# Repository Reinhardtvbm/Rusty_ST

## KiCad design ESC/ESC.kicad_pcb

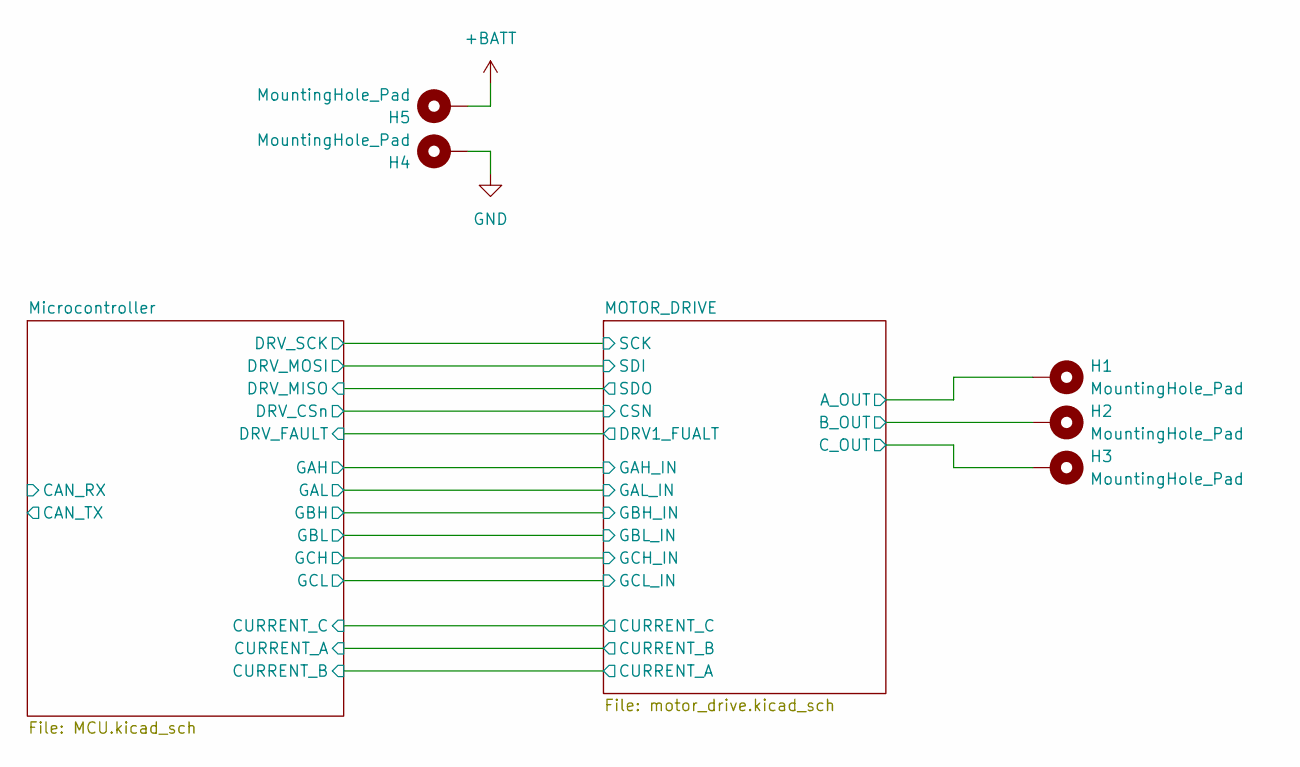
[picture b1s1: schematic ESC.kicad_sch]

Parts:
H1, H2, H3: MountingHole_Pad; Pad_3x4
H4, H5: MountingHole_Pad; Pad_THT_3x4

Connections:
+BATT: H5.1; also elsewhere on the board
/MOTOR_DRIVE/A_OUT: H1.1; also elsewhere on the board
/MOTOR_DRIVE/B_OUT: H2.1; also elsewhere on the board
/MOTOR_DRIVE/C_OUT: H3.1; also elsewhere on the board
GND: H4.1; also elsewhere on the board

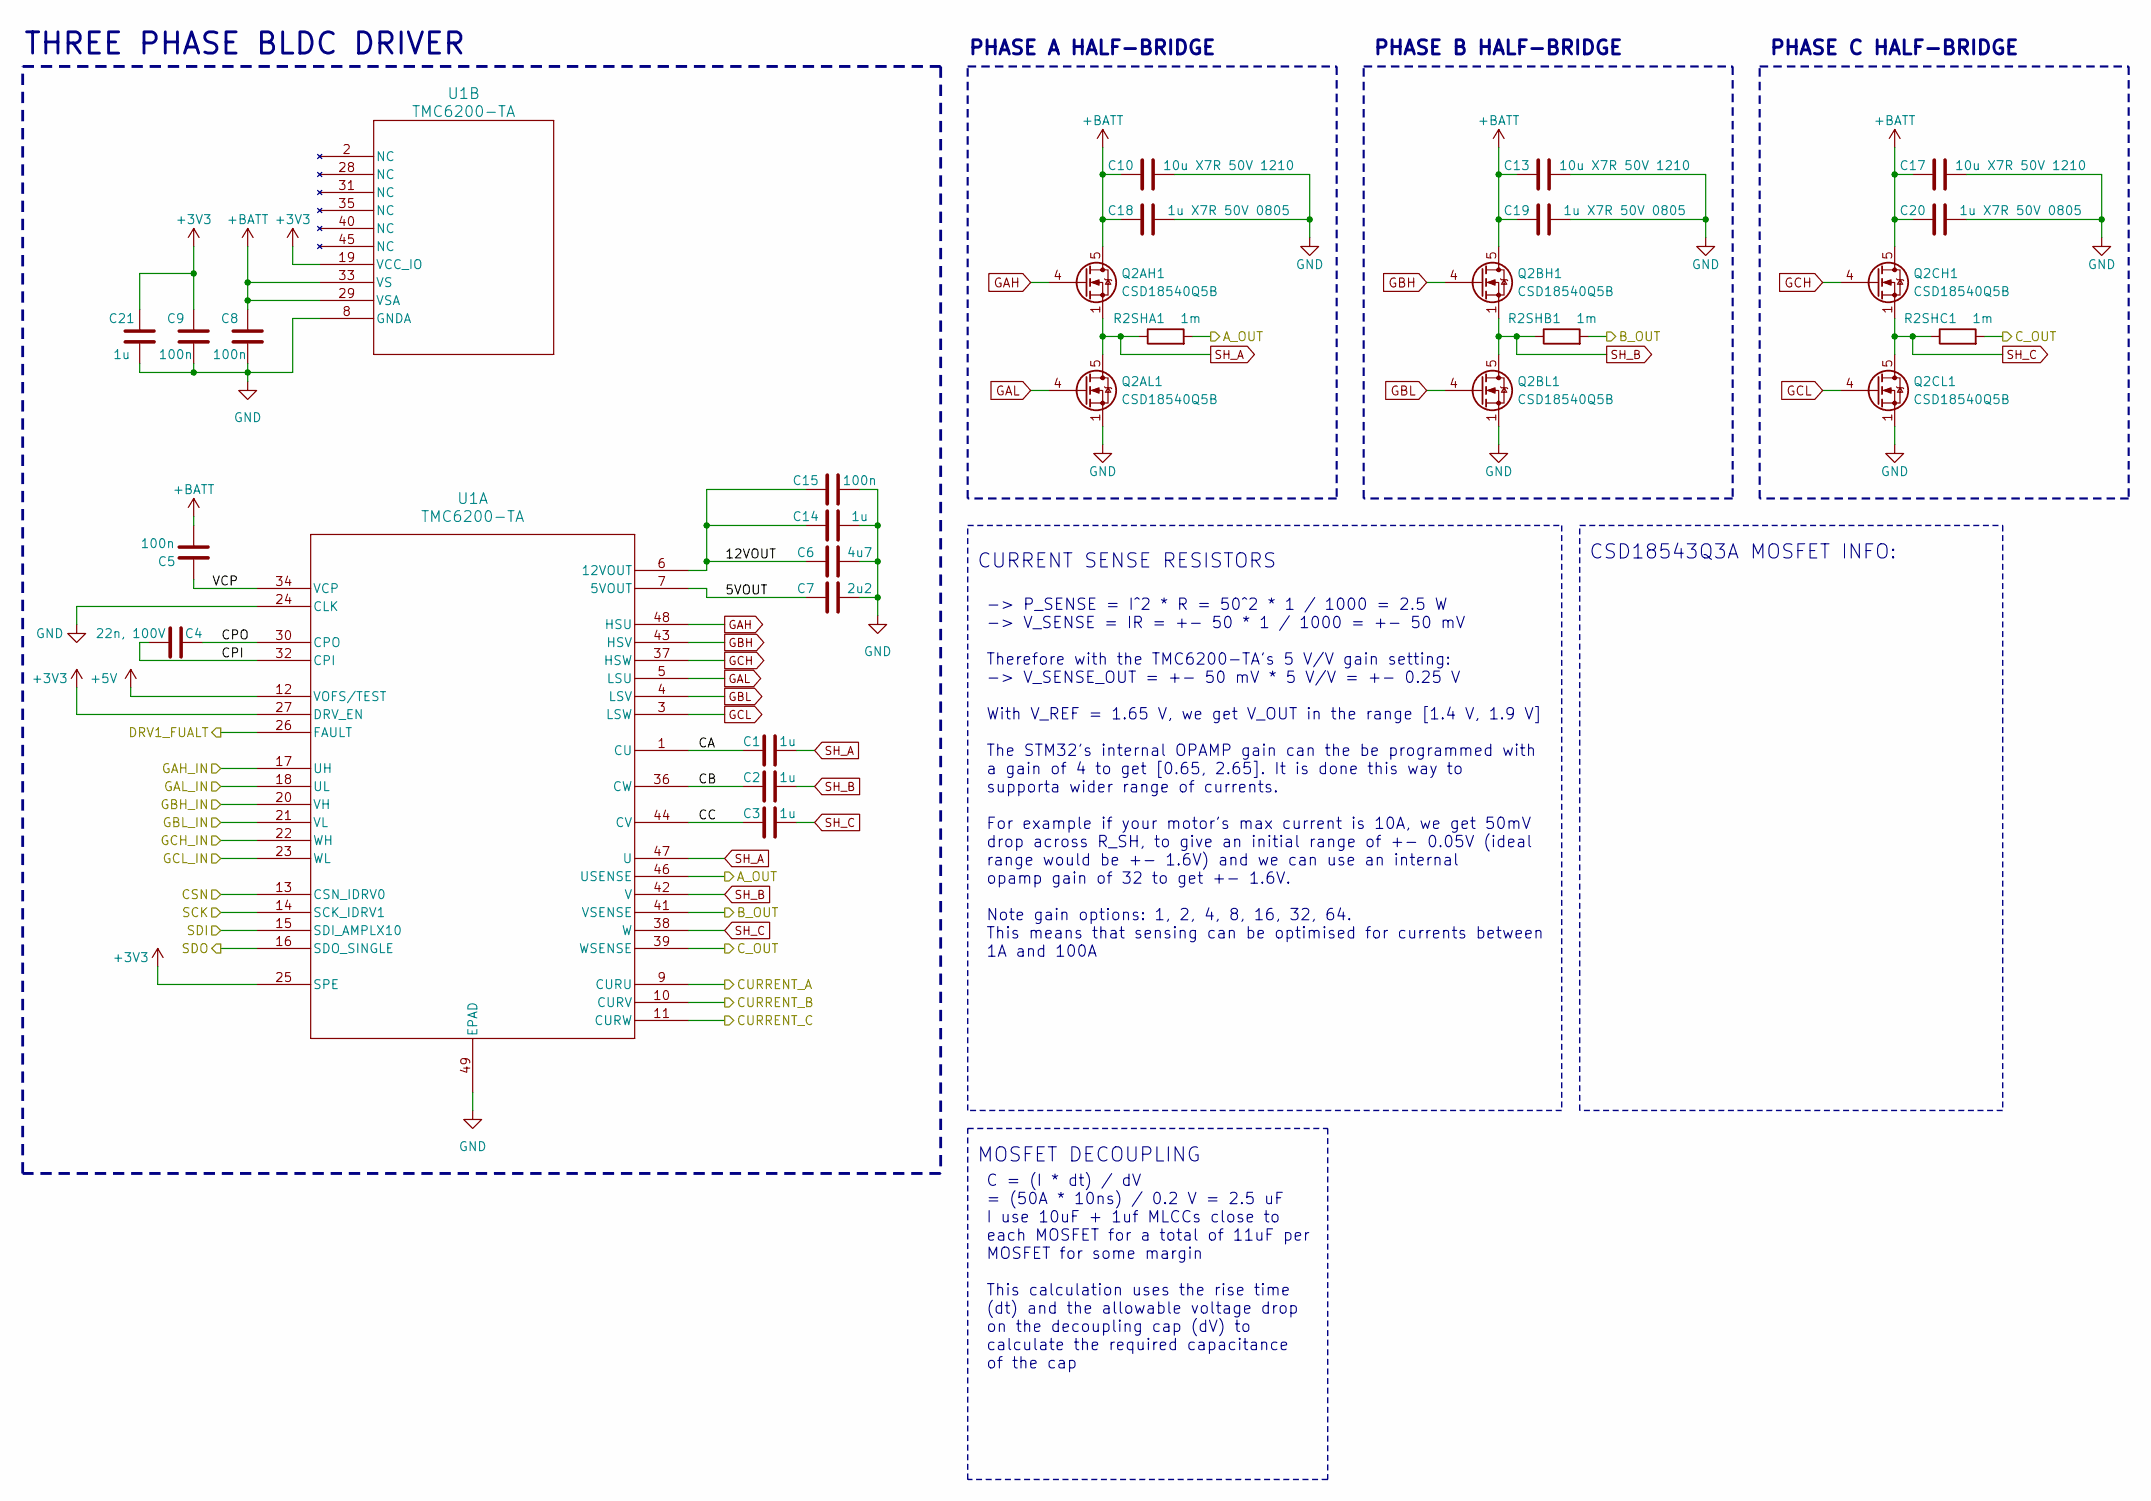
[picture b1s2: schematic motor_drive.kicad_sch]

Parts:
C1, C2, C3: 1u; C_0603_1608Metric
C4: 22n, 100V; C_0603_1608Metric
C5: 100n; C_0603_1608Metric
C6: 4u7; C_0603_1608Metric
C7: 2u2; C_0402_1005Metric
C8: 100n; C_0402_1005Metric
C9, C15: 100n; C_0201_0603Metric
C10, C13, C17: 10u X7R 50V 1210; C_1210_3225Metric
C14: 1u; C_0402_1005Metric
C18, C19, C20: 1u X7R 50V 0805; C_0805_2012Metric
C21: 1u; C_0201_0603Metric
Q2AH1, Q2AL1, Q2BH1, Q2BL1, Q2CH1, Q2CL1: CSD18540Q5B; TDSON-8-1
R2SHA1, R2SHB1, R2SHC1: 1m; R_2512_6332Metric
U1: TMC6200-TA; TQFP-48-1EP_7x7mm_P0.5mm_EP5x5mm

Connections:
+3V3: C9.2, C21.2, U1.19 (VCC_IO), U1.25 (SPE), U1.27 (DRV_EN); also elsewhere on the board
+5V: U1.12 (VOFS/TEST); also elsewhere on the board
+BATT: C5.2, C8.2, C10.1, C13.1, C17.1, C18.1, C19.1, C20.1, Q2AH1.5 (D), Q2BH1.5 (D), Q2CH1.5 (D), U1.29 (VSA), U1.33 (VS); also elsewhere on the board
/MOTOR_DRIVE/5VOUT: C7.2, U1.7 (5VOUT)
/MOTOR_DRIVE/12VOUT: C6.1, C14.2, C15.2, U1.6 (12VOUT)
/MOTOR_DRIVE/A_OUT: R2SHA1.2, U1.46 (USENSE); also elsewhere on the board
/MOTOR_DRIVE/B_OUT: R2SHB1.2, U1.41 (VSENSE); also elsewhere on the board
/MOTOR_DRIVE/CA: C1.1, U1.1 (CU)
/MOTOR_DRIVE/CB: C2.1, U1.36 (CW)
/MOTOR_DRIVE/CC: C3.1, U1.44 (CV)
/MOTOR_DRIVE/CPI: C4.2, U1.32 (CPI)
/MOTOR_DRIVE/CPO: C4.1, U1.30 (CPO)
/MOTOR_DRIVE/CSN: U1.13 (CSN_IDRV0); also elsewhere on the board
/MOTOR_DRIVE/CURRENT_A: U1.9 (CURU); also elsewhere on the board
/MOTOR_DRIVE/CURRENT_B: U1.10 (CURV); also elsewhere on the board
/MOTOR_DRIVE/CURRENT_C: U1.11 (CURW); also elsewhere on the board
/MOTOR_DRIVE/C_OUT: R2SHC1.2, U1.39 (WSENSE); also elsewhere on the board
/MOTOR_DRIVE/DRV1_FUALT: U1.26 (FAULT); also elsewhere on the board
/MOTOR_DRIVE/GAH_IN: U1.17 (UH); also elsewhere on the board
/MOTOR_DRIVE/GAL_IN: U1.18 (UL); also elsewhere on the board
/MOTOR_DRIVE/GBH_IN: U1.20 (VH); also elsewhere on the board
/MOTOR_DRIVE/GBL_IN: U1.21 (VL); also elsewhere on the board
/MOTOR_DRIVE/GCH_IN: U1.22 (WH); also elsewhere on the board
/MOTOR_DRIVE/GCL_IN: U1.23 (WL); also elsewhere on the board
/MOTOR_DRIVE/SCK: U1.14 (SCK_IDRV1); also elsewhere on the board
/MOTOR_DRIVE/SDI: U1.15 (SDI_AMPLX10); also elsewhere on the board
/MOTOR_DRIVE/SDO: U1.16 (SDO_SINGLE); also elsewhere on the board
/MOTOR_DRIVE/VCP: C5.1, U1.34 (VCP)
GAH: Q2AH1.4 (G), U1.48 (HSU)
GAL: Q2AL1.4 (G), U1.5 (LSU)
GBH: Q2BH1.4 (G), U1.43 (HSV)
GBL: Q2BL1.4 (G), U1.4 (LSV)
GCH: Q2CH1.4 (G), U1.37 (HSW)
GCL: Q2CL1.4 (G), U1.3 (LSW)
GND: C6.2, C7.1, C8.1, C9.1, C10.2, C13.2, C14.1, C15.1, C17.2, C18.2, C19.2, C20.2, C21.1, Q2AL1.1 (S), Q2AL1.2 (S), Q2AL1.3 (S), Q2BL1.1 (S), Q2BL1.2 (S), Q2BL1.3 (S), Q2CL1.1 (S), Q2CL1.2 (S), Q2CL1.3 (S), U1.8 (GNDA), U1.24 (CLK), U1.49 (EPAD); also elsewhere on the board
SH_A: C1.2, Q2AH1.1 (S), Q2AH1.2 (S), Q2AH1.3 (S), Q2AL1.5 (D), R2SHA1.1, U1.47 (U)
SH_B: C2.2, Q2BH1.1 (S), Q2BH1.2 (S), Q2BH1.3 (S), Q2BL1.5 (D), R2SHB1.1, U1.42 (V)
SH_C: C3.2, Q2CH1.1 (S), Q2CH1.2 (S), Q2CH1.3 (S), Q2CL1.5 (D), R2SHC1.1, U1.38 (W)

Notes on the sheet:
C = (I * dt) / dV = (50A * 10ns) / 0.2 V = 2.5 uF I use 10uF + 1uf MLCCs close to each MOSFET for a total of 11uF per MOSFET for some margin This calculation uses the rise time (dt) and the allowable voltage drop on the decoupling cap (dV) to calculate the required capacitance of the cap
-> P_SENSE = I^2 * R = 50^2 * 1 / 1000 = 2.5 W -> V_SENSE = IR = +- 50 * 1 / 1000 = +- 50 mV Therefore with the TMC6200-TA's 5 V/V gain setting: -> V_SENSE_OUT = +- 50 mV * 5 V/V = +- 0.25 V With V_REF = 1.65 V, we get V_OUT in the range [1.4 V, 1.9 V] The STM32's internal OPAMP gain can the be pro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
PHASE C HALF-BRIDGE
CURRENT SENSE RESISTORS
CSD18543Q3A MOSFET INFO:
PHASE B HALF-BRIDGE
THREE PHASE BLDC DRIVER
PHASE A HALF-BRIDGE
MOSFET DECOUPLING

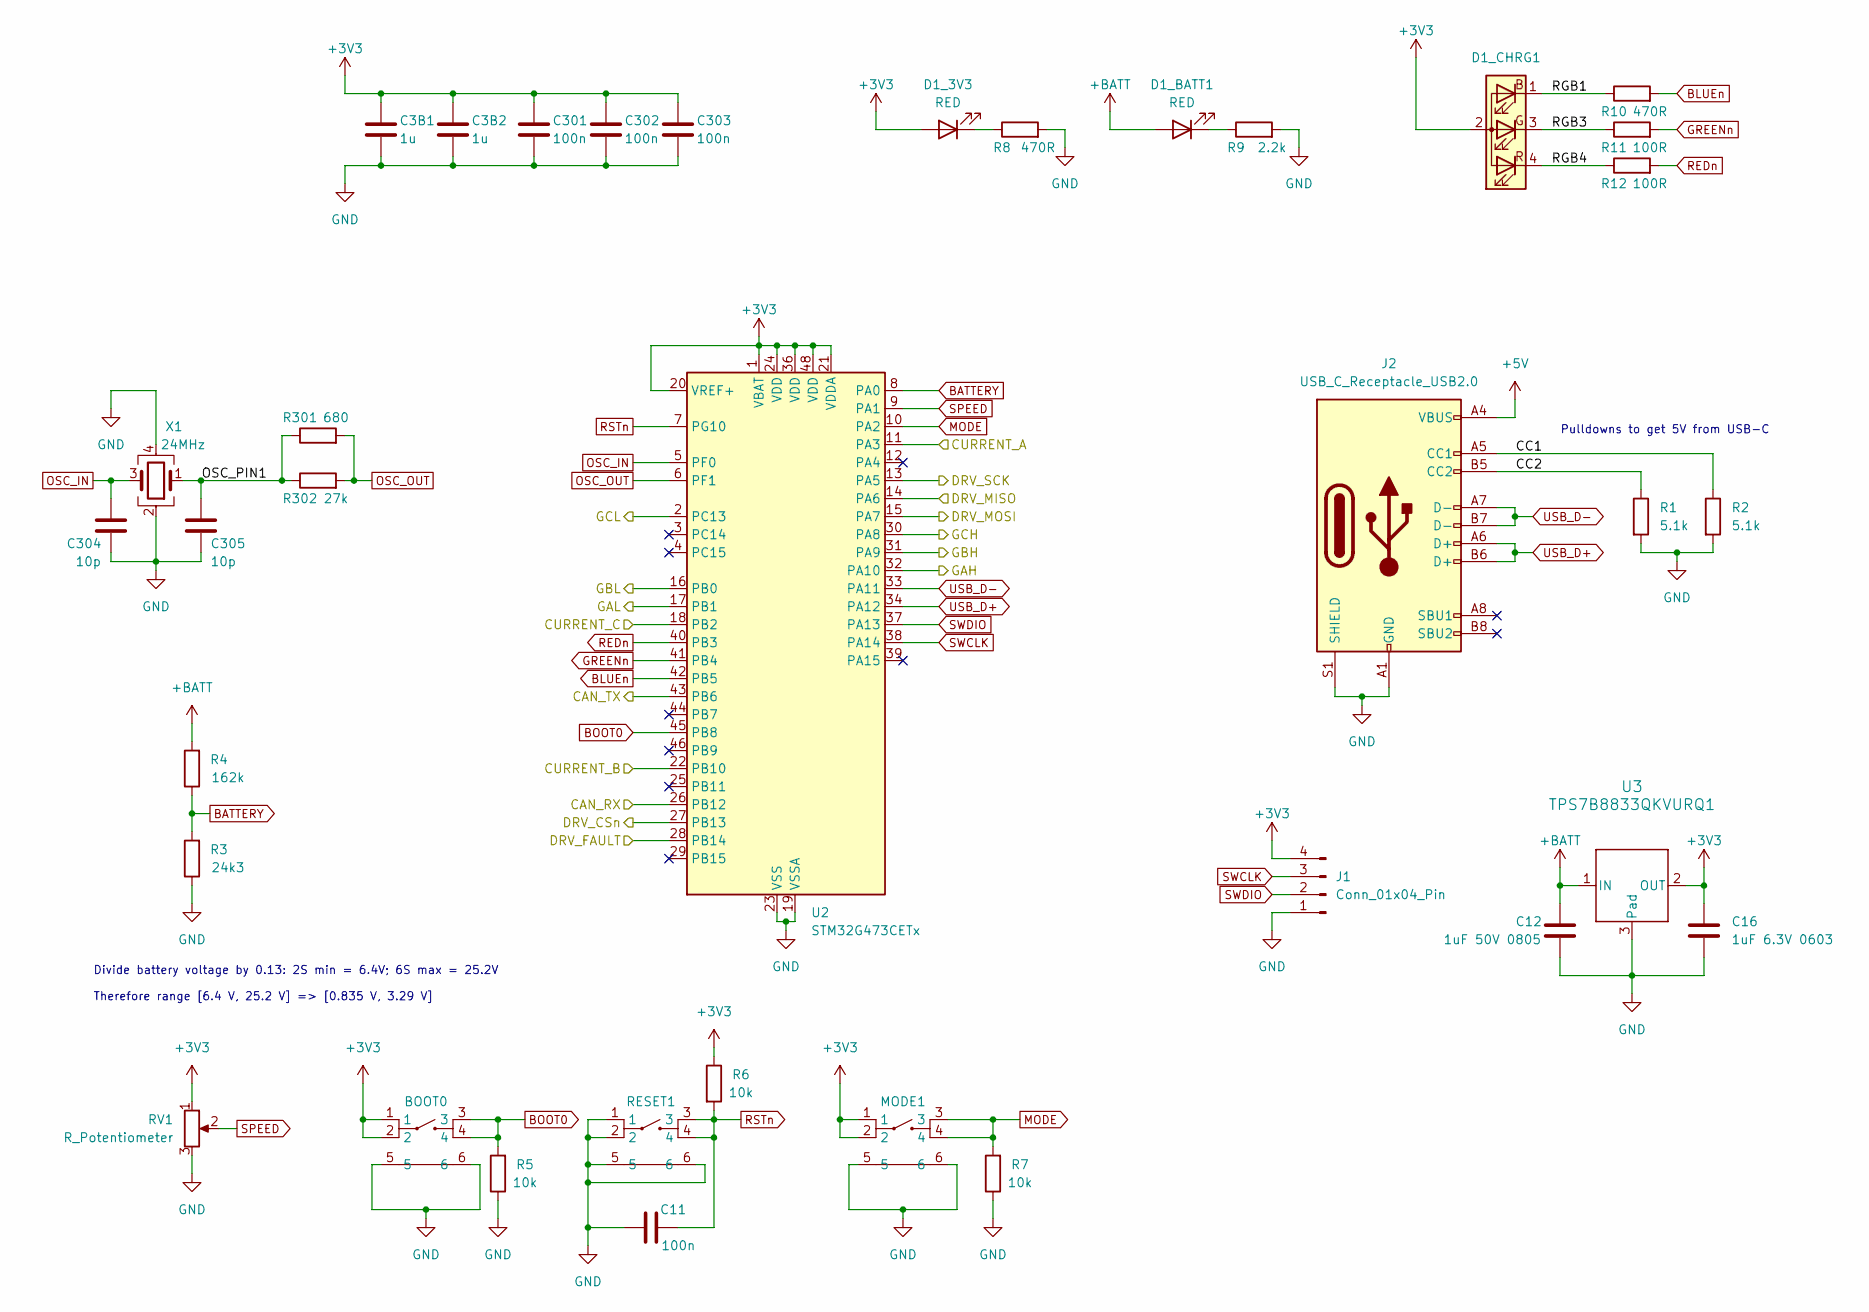
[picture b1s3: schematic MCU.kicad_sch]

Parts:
BOOT0: 435151014824; Wurth
C3B1, C3B2: 1u; C_0201_0603Metric
C11: 100n; C_0603_1608Metric
C12: 1uF 50V 0805; C_0805_2012Metric
C16: 1uF 6.3V 0603; C_0603_1608Metric
C301, C302, C303: 100n; C_0201_0603Metric
C304, C305: 10p; C_0603_1608Metric
D1_3V3, D1_BATT1: RED; LED_0603_1608Metric
D1_CHRG1: LED_BAGR; 150120M173000
J1: Conn_01x04_Pin; PinHeader_1x04_P2.54mm_Vertical
J2: USB_C_Receptacle_USB2.0; USB_C_Receptacle_GCT_USB4105-xx-A_16P_TopMnt_Horizontal
MODE1: 435151014824; Wurth
R1, R2: 5.1k; R_0603_1608Metric
R3: 24k3; R_0603_1608Metric
R4: 162k; R_0603_1608Metric
R5, R6, R7: 10k; R_0603_1608Metric
R8, R10: 470R; R_0603_1608Metric
R9: 2.2k; R_0603_1608Metric
R11, R12: 100R; R_0603_1608Metric
R301: 680; R_0603_1608Metric
R302: 27k; R_0603_1608Metric
RESET1: 435151014824; Wurth
RV1: R_Potentiometer; Potentiometer_Alps_RK09Y11_Single_Horizontal
U2: STM32G473CETx; LQFP-48_7x7mm_P0.5mm
U3: TPS7B8833QKVURQ1; KVU0003A-MFG
X1: 24MHz; Crystal_SMD_3225-4Pin_3.2x2.5mm

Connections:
+3V3: BOOT0.1, BOOT0.2, C3B1.1, C3B2.1, C16.1, C301.1, C302.1, C303.1, D1_3V3.2 (A), D1_CHRG1.2 (A), J1.4, MODE1.1, MODE1.2, R6.1, RV1.1, U2.1 (VBAT), U2.20 (VREF+), U2.21 (VDDA), U2.24 (VDD), U2.36 (VDD), U2.48 (VDD), U3.2 (OUT); also elsewhere on the board
+5V: J2.A4 (VBUS), J2.A9 (VBUS), J2.B4 (VBUS), J2.B9 (VBUS); also elsewhere on the board
+BATT: C12.1, D1_BATT1.2 (A), R4.2, U3.1 (IN); also elsewhere on the board
/MOTOR_DRIVE/CSN: U2.27 (PB13); also elsewhere on the board
/MOTOR_DRIVE/CURRENT_A: U2.22 (PB10); also elsewhere on the board
/MOTOR_DRIVE/CURRENT_B: U2.11 (PA3); also elsewhere on the board
/MOTOR_DRIVE/CURRENT_C: U2.18 (PB2); also elsewhere on the board
/MOTOR_DRIVE/DRV1_FUALT: U2.28 (PB14); also elsewhere on the board
/MOTOR_DRIVE/GAH_IN: U2.32 (PA10); also elsewhere on the board
/MOTOR_DRIVE/GAL_IN: U2.17 (PB1); also elsewhere on the board
/MOTOR_DRIVE/GBH_IN: U2.31 (PA9); also elsewhere on the board
/MOTOR_DRIVE/GBL_IN: U2.16 (PB0); also elsewhere on the board
/MOTOR_DRIVE/GCH_IN: U2.30 (PA8); also elsewhere on the board
/MOTOR_DRIVE/GCL_IN: U2.2 (PC13); also elsewhere on the board
/MOTOR_DRIVE/SCK: U2.13 (PA5); also elsewhere on the board
/MOTOR_DRIVE/SDI: U2.15 (PA7); also elsewhere on the board
/MOTOR_DRIVE/SDO: U2.14 (PA6); also elsewhere on the board
/Microcontroller/CAN_RX: U2.26 (PB12)
/Microcontroller/CAN_TX: U2.43 (PB6)
/Microcontroller/CC1: J2.A5 (CC1), R2.1
/Microcontroller/CC2: J2.B5 (CC2), R1.1
/Microcontroller/OSC_PIN1: C305.1, R301.1, R302.1, X1.1
/Microcontroller/RGB1: D1_CHRG1.1 (BK), R10.1
/Microcontroller/RGB3: D1_CHRG1.3 (GK), R11.1
/Microcontroller/RGB4: D1_CHRG1.4 (RK), R12.1
BATTERY: R3.2, R4.1, U2.8 (PA0)
BLUEn: R10.2, U2.42 (PB5)
BOOT0: BOOT0.3, BOOT0.4, R5.2, U2.45 (PB8)
GND: BOOT0.5, BOOT0.6, C3B1.2, C3B2.2, C11.1, C12.2, C16.2, C301.2, C302.2, C303.2, C304.2, C305.2, J1.1, J2.A1 (GND), J2.A12 (GND), J2.B1 (GND), J2.B12 (GND), J2.S1 (SHIELD), MODE1.5, MODE1.6, R1.2, R2.2, R3.1, R5.1, R7.1, R8.2, R9.2, RESET1.1, RESET1.2, RESET1.5, RESET1.6, RV1.3, U2.19 (VSSA), U2.23 (VSS), U2.35 (VSS), U2.47 (VSS), U3.3 (Pad), X1.2, X1.4; also elsewhere on the board
GREENn: R11.2, U2.41 (PB4)
MODE: MODE1.3, MODE1.4, R7.2, U2.10 (PA2)
unnamed: D1_3V3.1 (K), R8.1
unnamed: D1_BATT1.1 (K), R9.1
OSC_IN: C304.1, U2.5 (PF0), X1.3
OSC_OUT: R301.2, R302.2, U2.6 (PF1)
REDn: R12.2, U2.40 (PB3)
RSTn: C11.2, R6.2, RESET1.3, RESET1.4, U2.7 (PG10)
SPEED: RV1.2, U2.9 (PA1)
SWCLK: J1.3, U2.38 (PA14)
SWDIO: J1.2, U2.37 (PA13)
USB_D+: J2.A6 (D+), J2.B6 (D+), U2.34 (PA12)
USB_D-: J2.A7 (D-), J2.B7 (D-), U2.33 (PA11)

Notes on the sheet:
Divide battery voltage by 0.13: 2S min = 6.4V; 6S max = 25.2V Therefore range [6.4 V, 25.2 V] => [0.835 V, 3.29 V]
Pulldowns to get 5V from USB-C

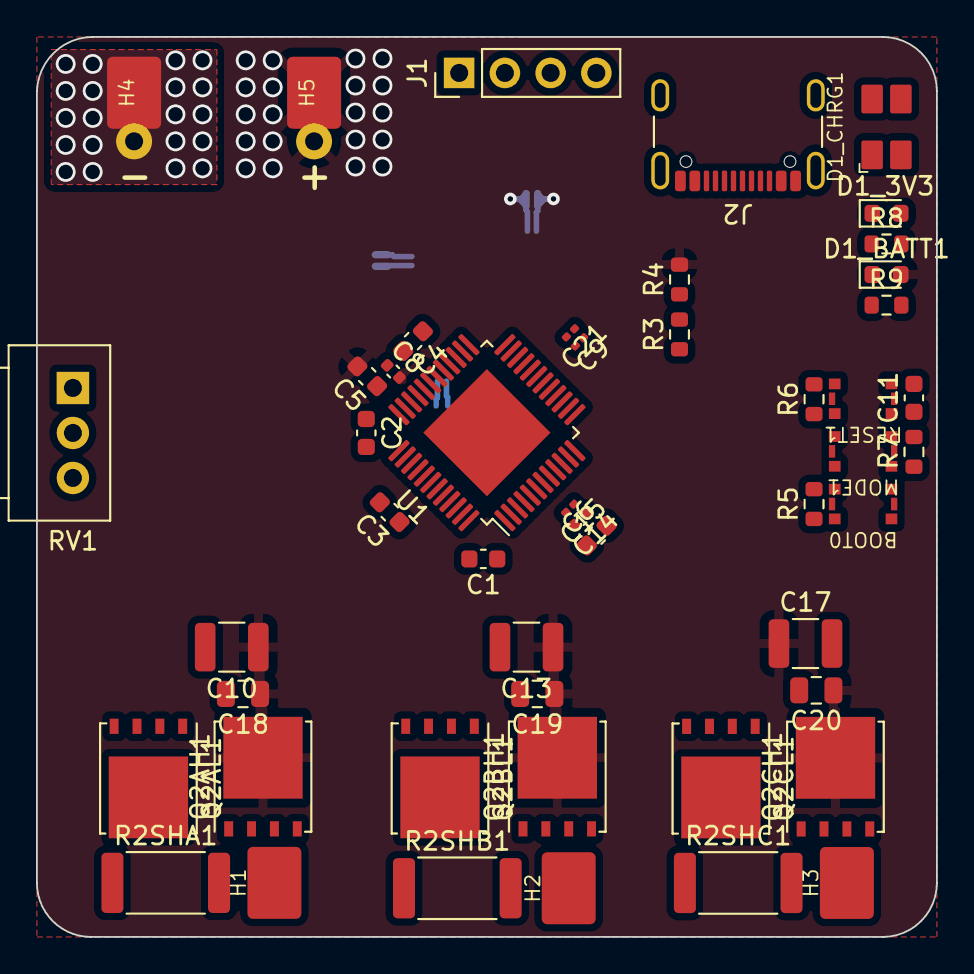
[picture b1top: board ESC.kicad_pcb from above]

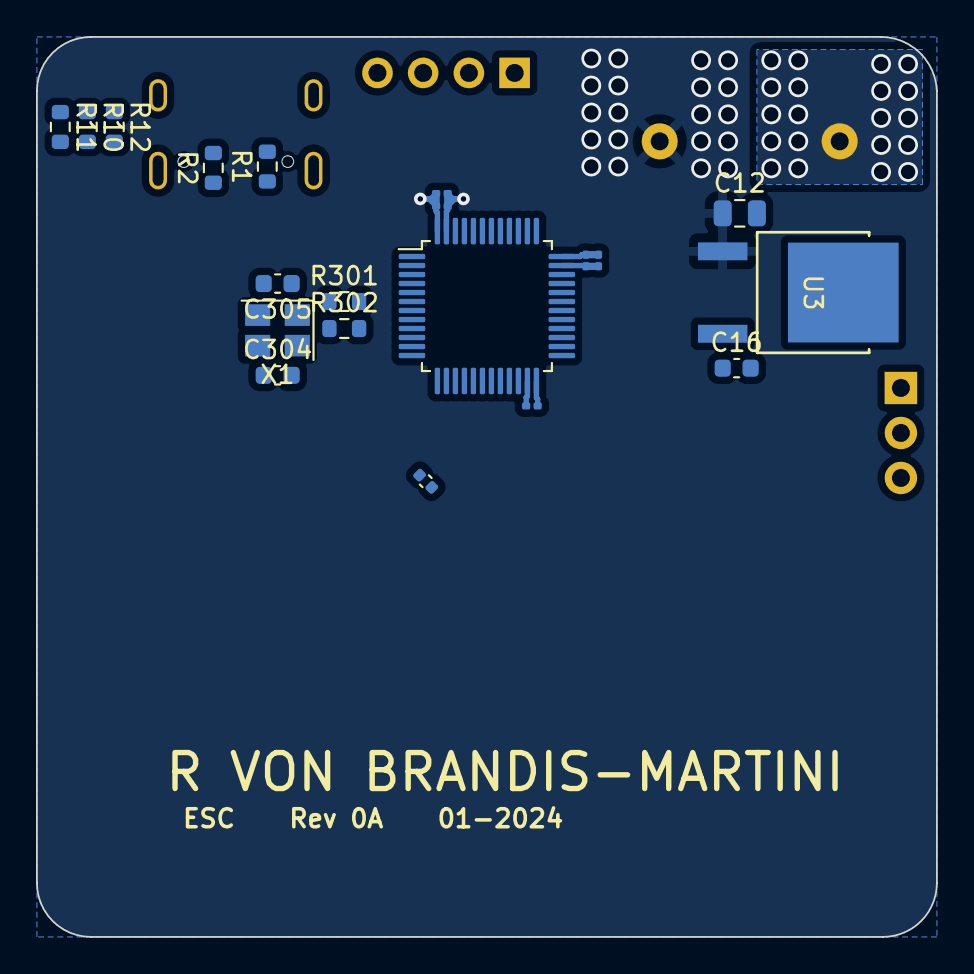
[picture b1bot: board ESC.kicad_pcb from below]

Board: 8 copper layers, 50.0 x 50.0 mm, 69 parts (20 on the bottom side), 60 nets.

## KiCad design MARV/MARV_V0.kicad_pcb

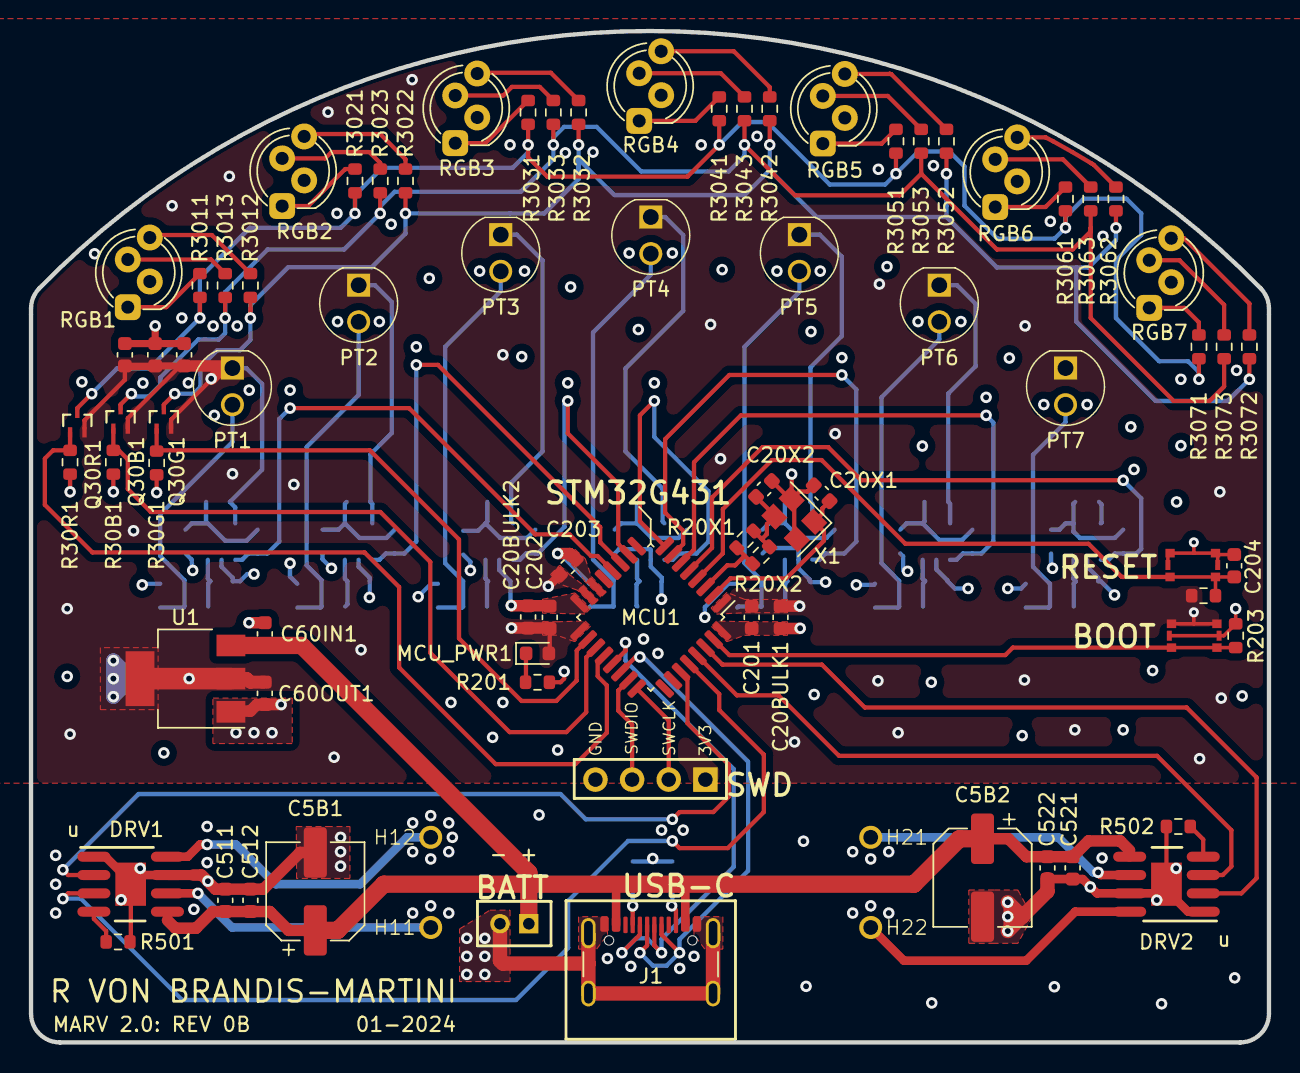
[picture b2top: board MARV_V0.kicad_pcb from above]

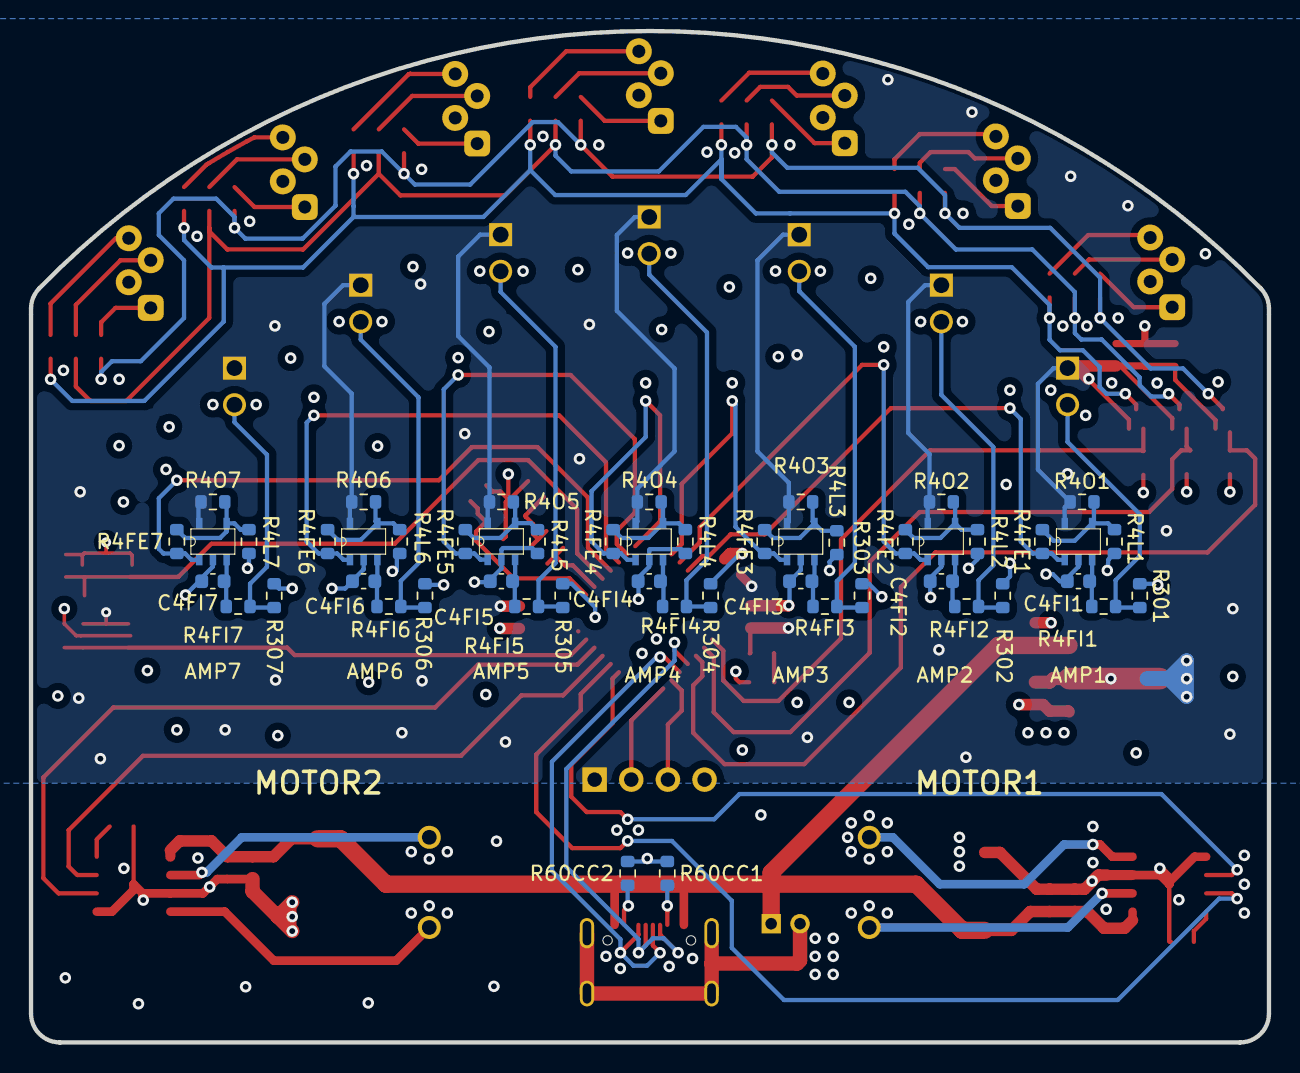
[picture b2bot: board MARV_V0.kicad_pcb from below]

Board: 4 copper layers, 85.8 x 70.1 mm, 133 parts (51 on the bottom side), 80 nets.

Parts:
AMP1, AMP2, AMP3, AMP4, AMP5, AMP6, AMP7: type="X" model="OPAMP" lib=""; DBV5_TEX-L
BOOT0: SW_Push; Wurth
C4FI1, C4FI2, C4FI3, C4FI4, C4FI5, C4FI6, C4FI7, C20BULK1, C20BULK2, C30B1, C30G1, C30R1, C60IN1, C60OUT1, C201, C202, C203, C204: C; C_0603_1608Metric
C5B1, C5B2: 100uF; CP_Elec_6.3x7.7
C20X1, C20X2: 10pF; C_0603_1608Metric
C511, C521: 10uF; C_0603_1608Metric
C512, C522: 1uF; C_0603_1608Metric
DRV1, DRV2: DRV8871DDA; DDA0008H_M
H11, H12, H21, H22: MountingHole_Pad; MountingHole_1.5mm_Pad_TopOnly
J1: USB_C_Receptacle; USB_C_Receptacle_GCT_USB4105-xx-A_16P_TopMnt_Horizontal
J2: Conn_01x02_Pin; PinHeader_1x02_P2.00mm_Vertical
MCU1: STM32G431KBT6; LQFP-32_7x7mm_P0.8mm
MCU_PWR1: LED; LED_0603_1608Metric
PT1, PT2, PT3, PT4, PT5, PT6, PT7: TEPT5600; LED_TEPT5600_VIS
Q30B1, Q30G1, Q30R1: NMOS; DMN26D0UT-7_PER-L
R4FE1, R4FE2, R4FE3, R4FE4, R4FE5, R4FE6, R4FE7, R4FI1, R4FI2, R4FI3, R4FI4, R4FI5, R4FI6, R4FI7, R4L1, R4L2, R4L3, R4L4, R4L5, R4L6, R4L7, R4O1, R4O2, R4O3, R4O4, R4O5, R4O6, R4O7, R30B1, R30G1, R30R1, R201, R202, R203, R301, R302, R303, R304, R305, R306, R307, R3011, R3012, R3013, R3021, R3022, R3023, R3031, R3032, R3033, R3041, R3042, R3043, R3051, R3052, R3053, R3061, R3062, R3063, R3071, R3072, R3073: R; R_0603_1608Metric
R20X1: 680; R_0603_1608Metric
R20X2: 27k; R_0603_1608Metric
R60CC1, R60CC2: 5.1k; R_0603_1608Metric
R501, R502: 32k; R_0603_1608Metric
RGB1, RGB2, RGB3, RGB4, RGB5, RGB6, RGB7: LED_RKGB; LED_D5.0mm-4_RGB_Staggered_Pins
RST1: SW_Push; Wurth
SWD1: SERIAL_WIRE_DEBUG; PinHeader_1x04_P2.54mm_Vertical
U1: LD1117S33TR_SOT223; SOT-223-3_TabPin2
X1: Crystal_24MHz; Crystal_SMD_3225-4Pin_3.2x2.5mm

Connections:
+3.3V: AMP1.5 (V+), AMP2.5 (V+), AMP3.5 (V+), AMP4.5 (V+), AMP5.5 (V+), AMP6.5 (V+), AMP7.5 (V+), BOOT0.1, BOOT0.2, C20BULK1.1, C20BULK2.1, C30B1.1, C30G1.1, C30R1.1, C60OUT1.1, C201.1, C202.1, C203.1, MCU1.1 (VDD), MCU1.15 (VDDA), MCU1.17 (VDD), MCU_PWR1.2 (A), PT1.1 (C), PT2.1 (C), PT3.1 (C), PT4.1 (C), PT5.1 (C), PT6.1 (C), PT7.1 (C), Q30B1.1 (D), Q30G1.1 (D), Q30R1.1 (D), R4O1.1, R4O2.1, R4O3.1, R4O4.1, R4O5.1, R4O6.1, R4O7.1, R202.1, SWD1.1, U1.2 (VO)
+BATT: C5B1.1, C5B2.1, C60IN1.1, C511.1, C512.1, C521.1, C522.1, DRV1.5 (VM), DRV2.5 (VM), J1.A4 (VBUS), J1.A9 (VBUS), J1.B4 (VBUS), J1.B9 (VBUS), J2.1, U1.3 (VI)
/MCU/BLUE_CTRL: MCU1.19 (PA9), Q30B1.2 (G), R30B1.1
/MCU/D+: J1.A6 (D+), J1.B6 (D+), MCU1.22 (PA12)
/MCU/D-: J1.A7 (D-), J1.B7 (D-), MCU1.21 (PA11)
/MCU/GREEN_CTRL: MCU1.18 (PA8), Q30G1.2 (G), R30G1.1
/MCU/IN_1: AMP1.1, MCU1.12 (PA7), R4FE1.1
/MCU/IN_2: AMP2.1, MCU1.11 (PA6), R4FE2.1
/MCU/IN_3: AMP3.1, MCU1.10 (PA5), R4FE3.1
/MCU/IN_4: AMP4.1, MCU1.8 (PA3), R4FE4.1
/MCU/IN_5: AMP5.1, MCU1.7 (PA2), R4FE5.1
/MCU/IN_6: AMP6.1, MCU1.6 (PA1), R4FE6.1
/MCU/IN_7: AMP7.1, MCU1.5 (PA0), R4FE7.1
/MCU/OSC_OUT0: C20X2.1, R20X1.2, R20X2.2, X1.3
/MCU/PWM_1_1: DRV1.3 (IN1), MCU1.28 (PB5)
/MCU/PWM_1_2: DRV1.2 (IN2), MCU1.27 (PB4)
/MCU/PWM_2_1: DRV2.3 (IN1), MCU1.29 (PB6)
/MCU/PWM_2_2: DRV2.2 (IN2), MCU1.30 (PB7)
/MCU/RED_CTRL: MCU1.20 (PA10), Q30R1.2 (G), R30R1.1
/MCU/SWCLK: MCU1.24 (PA14), SWD1.2
/MCU/SWDIO: MCU1.23 (PA13), SWD1.3
/MOTOR_DRIVER/ILIM1: DRV1.4 (ILIM), R501.2
/MOTOR_DRIVER/ILIM2: DRV2.4 (ILIM), R502.2
/MOTOR_DRIVER/MOTOR1_OUT_1: DRV1.6 (OUT1), H11.1
/MOTOR_DRIVER/MOTOR1_OUT_2: DRV1.8 (OUT2), H12.1
/MOTOR_DRIVER/MOTOR2_OUT_1: DRV2.6 (OUT1), H21.1
/MOTOR_DRIVER/MOTOR2_OUT_2: DRV2.8 (OUT2), H22.1
/SENSOR/B1: R3013.1, RGB1.3 (BA)
/SENSOR/B2: R3023.1, RGB2.3 (BA)
/SENSOR/B3: R3033.1, RGB3.3 (BA)
/SENSOR/B4: R3043.1, RGB4.3 (BA)
/SENSOR/B5: R3053.1, RGB5.3 (BA)
/SENSOR/B6: R3063.1, RGB6.3 (BA)
/SENSOR/B7: R3073.1, RGB7.3 (BA)
/SENSOR/BLUE: Q30B1.3 (S), R3013.2, R3023.2, R3033.2, R3043.2, R3053.2, R3063.2, R3073.2
/SENSOR/G1: R3012.1, RGB1.4 (GA)
/SENSOR/G2: R3022.1, RGB2.4 (GA)
/SENSOR/G3: R3032.1, RGB3.4 (GA)
/SENSOR/G4: R3042.1, RGB4.4 (GA)
/SENSOR/G5: R3052.1, RGB5.4 (GA)
/SENSOR/G6: R3062.1, RGB6.4 (GA)
/SENSOR/G7: R3072.1, RGB7.4 (GA)
/SENSOR/GREEN: Q30G1.3 (S), R3012.2, R3022.2, R3032.2, R3042.2, R3052.2, R3062.2, R3072.2
/SENSOR/R1: R3011.2, RGB1.1 (RA)
/SENSOR/R2: R3021.1, RGB2.1 (RA)
/SENSOR/R3: R3031.1, RGB3.1 (RA)
/SENSOR/R4: R3041.1, RGB4.1 (RA)
/SENSOR/R5: R3051.1, RGB5.1 (RA)
/SENSOR/R6: R3061.1, RGB6.1 (RA)
/SENSOR/R7: R3071.1, RGB7.1 (RA)
/SENSOR/RED: Q30R1.3 (S), R3011.1, R3021.2, R3031.2, R3041.2, R3051.2, R3061.2, R3071.2
/SENSOR/gain_offset/AMP2N: AMP2.4 (-), R4FE2.2, R4L2.2, R4O2.2
/SENSOR/gain_offset/AMP3N: AMP3.4 (-), R4FE3.2, R4L3.2, R4O3.2
/SENSOR/gain_offset/AMP4N: AMP4.4 (-), R4FE4.2, R4L4.2, R4O4.2
/SENSOR/gain_offset/AMP5N: AMP5.4 (-), R4FE5.2, R4L5.2, R4O5.2
/SENSOR/gain_offset/AMP6N: AMP6.4 (-), R4FE6.2, R4L6.2, R4O6.2
/SENSOR/gain_offset/AMP7N: AMP7.4 (-), R4FE7.2, R4L7.2, R4O7.2
/SENSOR/gain_offset/IN_1_FILT: AMP1.3 (+), C4FI1.1, R4FI1.2
/SENSOR/gain_offset/IN_2_FILT: AMP2.3 (+), C4FI2.1, R4FI2.2
/SENSOR/gain_offset/IN_3_FILT: AMP3.3 (+), C4FI3.1, R4FI3.2
/SENSOR/gain_offset/IN_4_FILT: AMP4.3 (+), C4FI4.1, R4FI4.2
/SENSOR/gain_offset/IN_5_FILT: AMP5.3 (+), C4FI5.1, R4FI5.2
/SENSOR/gain_offset/IN_6_FILT: AMP6.3 (+), C4FI6.1, R4FI6.2
/SENSOR/gain_offset/IN_7_FILT: AMP7.3 (+), C4FI7.1, R4FI7.2
/SENSOR/gain_offset/V_IN_1: PT1.2 (E), R4FI1.1, R301.1
/SENSOR/gain_offset/V_IN_2: PT2.2 (E), R4FI2.1, R302.1
/SENSOR/gain_offset/V_IN_3: PT3.2 (E), R4FI3.1, R303.1
/SENSOR/gain_offset/V_IN_4: PT4.2 (E), R4FI4.1, R304.1
/SENSOR/gain_offset/V_IN_5: PT5.2 (E), R4FI5.1, R305.1
/SENSOR/gain_offset/V_IN_6: PT6.2 (E), R4FI6.1, R306.1
/SENSOR/gain_offset/V_IN_7: PT7.2 (E), R4FI7.1, R307.1
BOOT0: BOOT0.3, BOOT0.4, MCU1.31 (PB8-BOOT0), R203.1
GND: AMP1.2 (V-), AMP2.2 (V-), AMP3.2 (V-), AMP4.2 (V-), AMP5.2 (V-), AMP6.2 (V-), AMP7.2 (V-), BOOT0.5, BOOT0.6, C4FI1.2, C4FI2.2, C4FI3.2, C4FI4.2, C4FI5.2, C4FI6.2, C4FI7.2, C5B1.2, C5B2.2, C20BULK1.2, C20BULK2.2, C20X1.2, C20X2.2, C30B1.2, C30G1.2, C30R1.2, C60IN1.2, C60OUT1.2, C201.2, C202.2, C203.2, C204.1, C511.2, C512.2, C521.2, C522.2, DRV1.1 (GND), DRV1.7 (PGND), DRV1.9 (PAD), DRV2.1 (GND), DRV2.7 (PGND), DRV2.9 (PAD), J1.A1 (GND), J1.A12 (GND), J1.B1 (GND), J1.B12 (GND), J1.S1 (SHIELD), J2.2, MCU1.14 (VSSA), MCU1.16 (VSS), MCU1.32 (VSS), R4L1.1, R4L2.1, R4L3.1, R4L4.1, R4L5.1, R4L6.1, R4L7.1, R30B1.2, R30G1.2, R30R1.2, R60CC1.2, R60CC2.2, R201.2, R203.2, R301.2, R302.2, R303.2, R304.2, R305.2, R306.2, R307.2, R501.1, R502.1, RGB1.2 (K), RGB2.2 (K), RGB3.2 (K), RGB4.2 (K), RGB5.2 (K), RGB6.2 (K), RGB7.2 (K), RST1.1, RST1.2, RST1.5, RST1.6, SWD1.4, U1.1 (GND), X1.2, X1.4
unnamed: AMP1.4 (-), R4FE1.2, R4L1.2, R4O1.2
unnamed: J1.A5 (CC1), R60CC1.1
unnamed: J1.B5 (CC2), R60CC2.1
unnamed: MCU_PWR1.1 (K), R201.1
OSC_IN: C20X1.1, MCU1.2 (PF0-OSC_IN), X1.1
OSC_OUT: MCU1.3 (PF1-OSC_OUT), R20X1.1, R20X2.1
RST: C204.2, MCU1.4 (PG10-NRST), R202.2, RST1.3, RST1.4

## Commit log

2024-01-21 ESC PDF
2024-03-24 removing files
2024-03-24 added ADCHandle::set_resolution. Not sure if there is a way to do what I want without unsafe
2024-03-25 created a macro which generates the set functions for an ADC's config
2024-03-27 created a procedural macro to generate arbitrary set functions for any field of any register
